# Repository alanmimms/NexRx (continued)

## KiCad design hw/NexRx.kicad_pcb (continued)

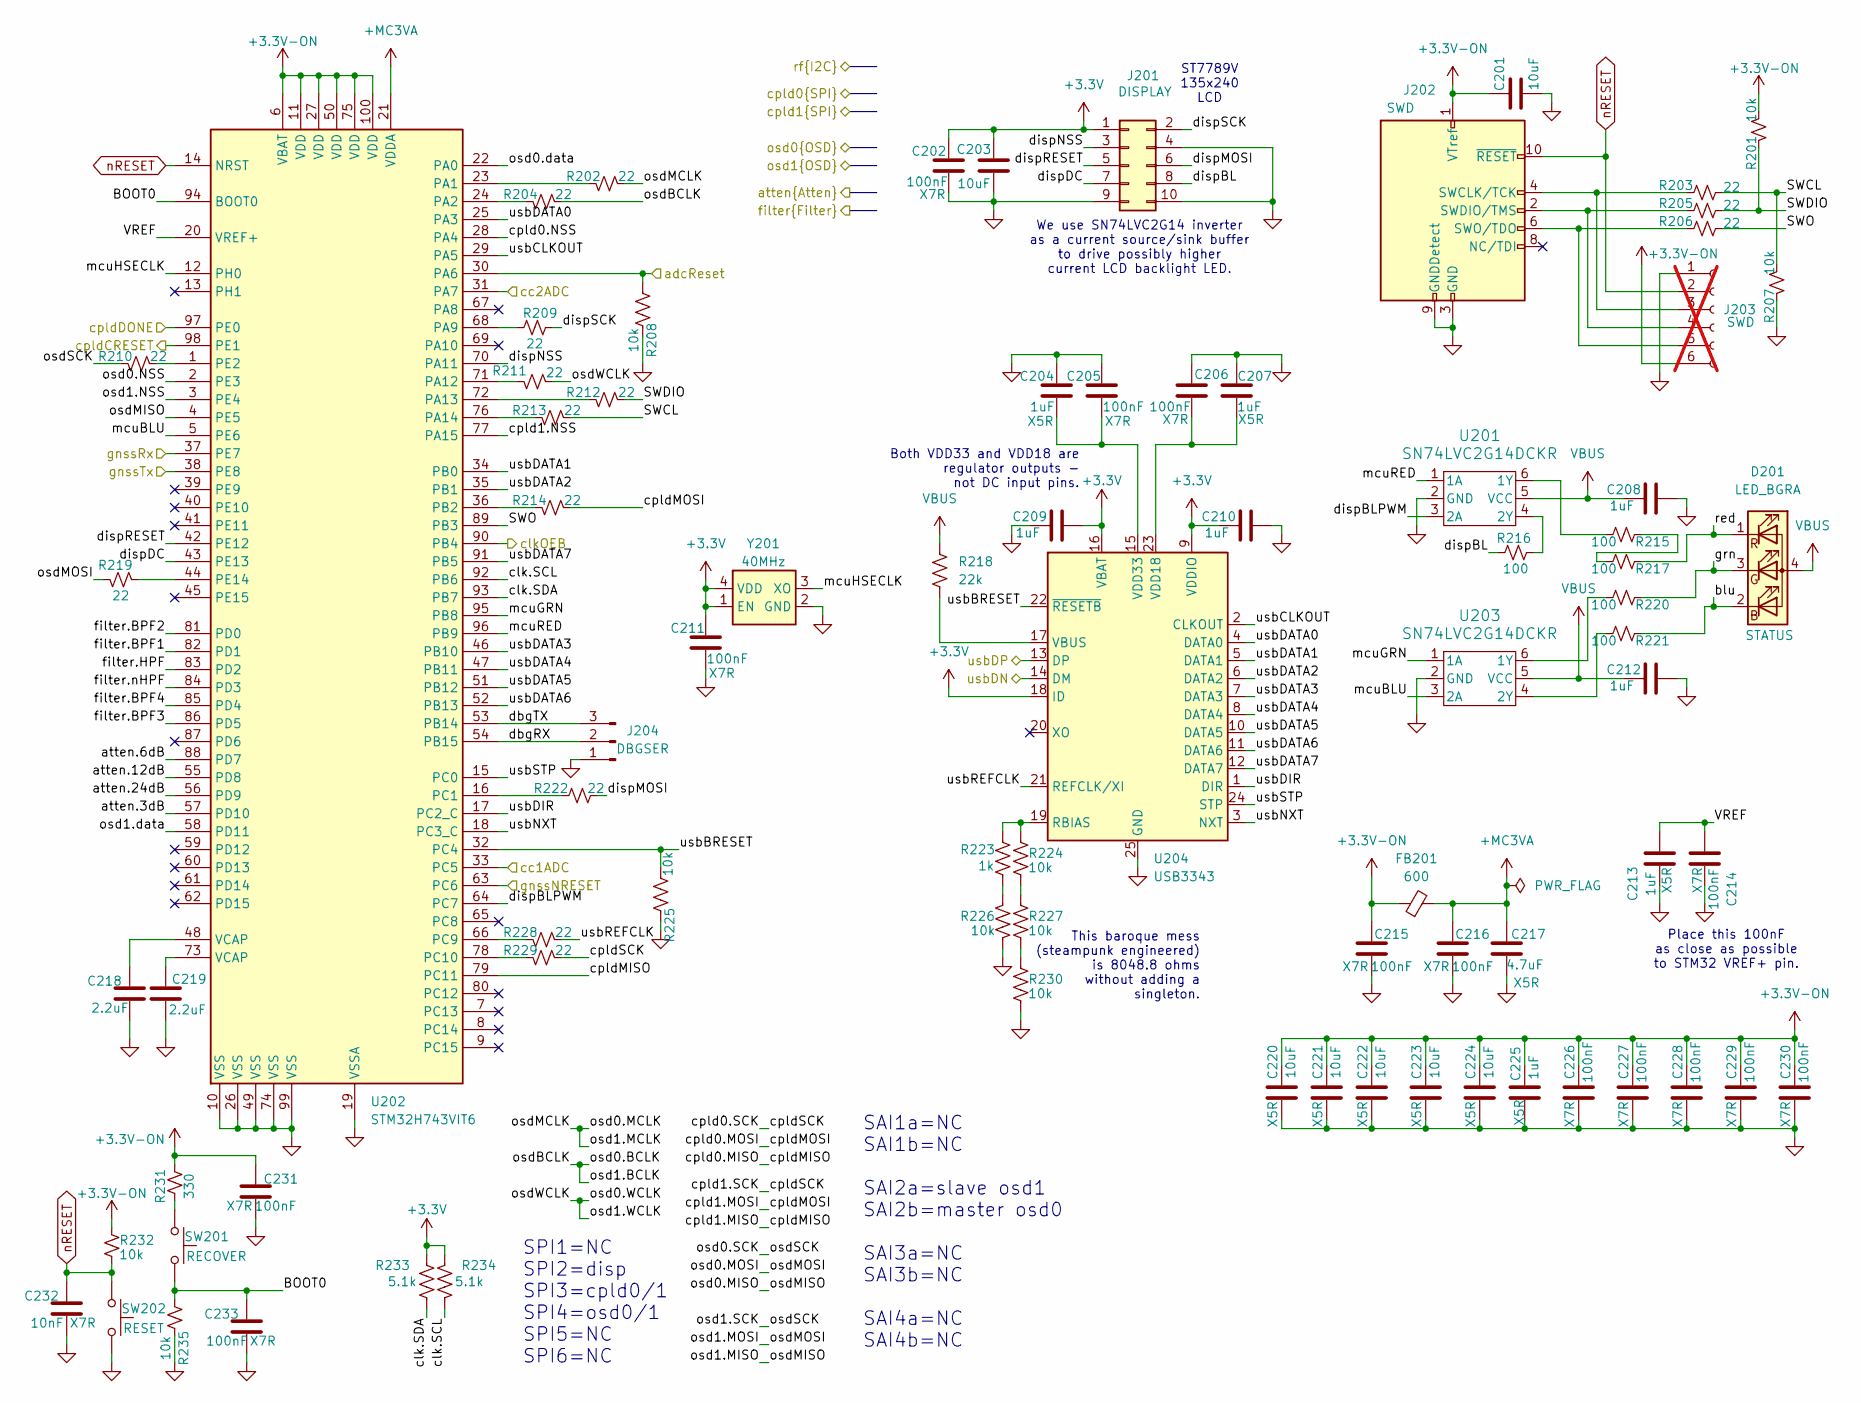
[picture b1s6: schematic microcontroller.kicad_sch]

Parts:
C201: 10uF; C_0402_1005Metric; MPN CL05A106MP6NUN8; LCSC_PN C76991
C202, C205, C206, C211, C215, C216, C230: 100nF; C_0402_1005Metric; MPN GCM155R71H104KE02D; LCSC_PN C307331
C203, C220, C221, C222, C223, C224: 10uF; C_0402_1005Metric; Mouser Part Number 187-CL05A106MP6NUN8
C204, C207, C208, C209, C210, C212: 1uF; C_0402_1005Metric; Mouser Part Number 81-GRM155R61E105MA2D
C213, C225: 1uF; C_0402_1005Metric; MPN GRM155R61E105MA12D; LCSC_PN C77009
C214, C226, C227, C228, C229, C231, C233: 100nF; C_0402_1005Metric; Mouser Part Number 81-GCM155R71H104KE2D
C217: 4.7uF; C_0402_1005Metric; MPN CM05X5R475M10AH; LCSC_PN C23733
C218, C219: 2.2uF; C_0402_1005Metric; MPN TMK105CBJ225MV-F; LCSC_PN C12530
C232: 10nF; C_0402_1005Metric; Mouser Part Number 81-GCM155R71H104KE2D
D201: LED_BGRA; WL-SFCD_0606; Mouser_PN 941-UHD1AA3K3E3V53Z3
FB201: 600; L_0603_1608Metric; MPN MI0603J601R-10; LCSC_PN C1006
J201: Conn_01x05_Pin; IDC-Header_2x05_P2.54mm_Vertical_SMD; LCSC_PN C32713285
J202: FTSH-105-01-L-DV-K; FTSH10501LDVK; MPN FTSH-105-01-L-DV-K; LCSC_PN C5155080
J203: SWD; PinHeader_1x06_P2.54mm_Vertical; not fitted
J204: DBGSER; PinHeader_1x03_P2.54mm_Vertical
R201, R207, R208, R224, R225, R226, R227, R230, R232, R235: 10k; R_0402_1005Metric; MPN RT0402BRD0710KL; LCSC_PN C283961
R202, R204: 22; R_0402_1005Metric; MPN 560112110216; LCSC_PN C25092
R203, R205, R206, R209, R210, R211, R212, R213, R214, R219, R222, R228, R229: 22; R_0402_1005Metric; MPN 560112110216; JLCPCBpn C4258780
R215, R216, R217, R220, R221: 100; R_0402_1005Metric; MPN MCS04020C1000FE000; Mouser Part Number 594-MCS04020C1000FE0
R218: 22k; R_0402_1005Metric; LCSC_PN C25768
R223: 1k; R_0402_1005Metric; MPN RP0402FRE071KL; LCSC_PN C11702
R231: 330; R_0402_1005Metric; MPN RC0402JR-7D330RL; LCSC_PN C25104
R233, R234: 5.1k; R_0402_1005Metric; MPN AC0402FR-7W5K1L; LCSC_PN C854378
SW201: RECOVER; SW_SPST_TS-1088-AR2016
SW202: RESET; SW_SPST_TS-1088-AR2016
U201, U203: SN74LVC2G14DCKR; SOIC_G14DCK3_TEX; LCSC_PN C37361
U202: STM32H743VIT6; LQFP-100_14x14mm_P0.5mm; MPN STM32H743VIT6; LCSC_PN C114409
U204: USB3343; QFN-24-1EP_4x4mm_P0.5mm_EP2.6x2.6mm; MPN USB3343-CP-TR; LCSC_PN C633347
Y201: 40MHz; ECSTXO201633400TR; MPN ECS-TXO-2016-33-400-TR; LCSC_PN C2451471

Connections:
+3.3V: C201.2, C202.1, C203.2, C209.2, C210.1, C211.1, C215.1, C220.1, C221.1, C222.1, C223.1, C224.1, C225.1, C226.1, C227.1, C228.1, C229.1, C230.1, C231.1, FB201.1, J201.1, J202.1 (VTref), J203.6, R201.1, R231.1, R232.1, R233.1, R234.1, U202.6 (VBAT), U202.11 (VDD), U202.27 (VDD), U202.50 (VDD), U202.75 (VDD), U202.100 (VDD), U204.9 (VDDIO), U204.16 (VBAT), U204.18 (ID), Y201.1 (EN), Y201.4 (VDD); also elsewhere on the board
+MC3VA: C216.1, C217.1, FB201.2, U202.21 (VDDA)
/Clock/clkOEB: U202.90 (PB4); also elsewhere on the board
/Filters/en.BPF1: U202.82 (PD1); also elsewhere on the board
/Filters/en.BPF2: U202.81 (PD0); also elsewhere on the board
/Filters/en.BPF3: U202.86 (PD5); also elsewhere on the board
/Filters/en.BPF4: U202.85 (PD4); also elsewhere on the board
/Filters/en.HPF: U202.83 (PD2); also elsewhere on the board
/Filters/en.nHPF: U202.84 (PD3); also elsewhere on the board
/Power/cc1ADC: U202.33 (PC5); also elsewhere on the board
/Power/cc2ADC: U202.31 (PA7); also elsewhere on the board
/Power/usbDN: U204.14 (DM); also elsewhere on the board
/Power/usbDP: U204.13 (DP); also elsewhere on the board
/atten.3dB: U202.57 (PD10); also elsewhere on the board
/atten.6dB: U202.88 (PD7); also elsewhere on the board
/atten.12dB: U202.55 (PD8); also elsewhere on the board
/atten.24dB: U202.56 (PD9); also elsewhere on the board
/cpld0/cpld.NSS: U202.28 (PA4); also elsewhere on the board
/cpld0/cpldCRESET: U202.98 (PE1); also elsewhere on the board
/cpld0/cpldDONE: U202.97 (PE0); also elsewhere on the board
/cpld0/osd.NSS: U202.2 (PE3); also elsewhere on the board
/cpld0/osd.data: U202.22 (PA0); also elsewhere on the board
/cpld1/cpld.MISO: U202.79 (PC11); also elsewhere on the board
/cpld1/cpld.MOSI: R214.1; also elsewhere on the board
/cpld1/cpld.NSS: U202.77 (PA15); also elsewhere on the board
/cpld1/cpld.SCK: R229.1; also elsewhere on the board
/cpld1/osd.BCLK: R204.1; also elsewhere on the board
/cpld1/osd.MCLK: R202.1; also elsewhere on the board
/cpld1/osd.MISO: U202.4 (PE5); also elsewhere on the board
/cpld1/osd.MOSI: R219.2; also elsewhere on the board
/cpld1/osd.NSS: U202.3 (PE4); also elsewhere on the board
/cpld1/osd.SCK: R210.2; also elsewhere on the board
/cpld1/osd.WCLK: R211.2; also elsewhere on the board
/cpld1/osd.data: U202.58 (PD11); also elsewhere on the board
/microcontroller/BOOT0: C233.1, R235.1, SW201.2, U202.94 (BOOT0)
/microcontroller/SWCL: R203.2, R207.1, R213.1
/microcontroller/SWDIO: R201.2, R205.2, R212.1
/microcontroller/SWO: R206.2, U202.89 (PB3)
/microcontroller/VREF: C213.1, C214.1, U202.20 (VREF+)
/microcontroller/adcReset: R208.1, U202.30 (PA6); also elsewhere on the board
/microcontroller/blu: D201.2 (BK), R221.1
/microcontroller/clk.SCL: R234.2, U202.92 (PB6)
/microcontroller/clk.SDA: R233.2, U202.93 (PB7)
/microcontroller/dbgRX: J204.2, U202.54 (PB15)
/microcontroller/dbgTX: J204.3, U202.53 (PB14)
/microcontroller/dispBL: J201.8, R216.2
/microcontroller/dispBLPWM: U201.3 (2A), U202.64 (PC7)
/microcontroller/dispDC: J201.7, U202.43 (PE13)
/microcontroller/dispMOSI: J201.6, R222.2
/microcontroller/dispNSS: J201.3, U202.70 (PA11)
/microcontroller/dispRESET: J201.5, U202.42 (PE12)
/microcontroller/dispSCK: J201.2, R209.2
/microcontroller/gnssNRESET: U202.63 (PC6); also elsewhere on the board
/microcontroller/gnssRx: U202.37 (PE7); also elsewhere on the board
/microcontroller/gnssTx: U202.38 (PE8); also elsewhere on the board
/microcontroller/grn: D201.3 (GK), R220.1
/microcontroller/mcuBLU: U202.5 (PE6), U203.3 (2A)
/microcontroller/mcuGRN: U202.95 (PB8), U203.1 (1A)
/microcontroller/mcuHSECLK: U202.12 (PH0), Y201.3 (XO)
/microcontroller/mcuRED: U201.1 (1A), U202.96 (PB9)
/microcontroller/red: D201.1 (RK), R217.1
/microcontroller/usbBRESET: R225.1, U202.32 (PC4), U204.22 (~RESETB)
/microcontroller/usbCLKOUT: U202.29 (PA5), U204.2 (CLKOUT)
/microcontroller/usbDATA0: U202.25 (PA3), U204.4 (DATA0)
/microcontroller/usbDATA1: U202.34 (PB0), U204.5 (DATA1)
/microcontroller/usbDATA2: U202.35 (PB1), U204.6 (DATA2)
/microcontroller/usbDATA3: U202.46 (PB10), U204.7 (DATA3)
/microcontroller/usbDATA4: U202.47 (PB11), U204.8 (DATA4)
/microcontroller/usbDATA5: U202.51 (PB12), U204.10 (DATA5)
/microcontroller/usbDATA6: U202.52 (PB13), U204.11 (DATA6)
/microcontroller/usbDATA7: U202.91 (PB5), U204.12 (DATA7)
/microcontroller/usbDIR: U202.17 (PC2_C), U204.1 (DIR)
/microcontroller/usbNXT: U202.18 (PC3_C), U204.3 (NXT)
/microcontroller/usbREFCLK: R228.1, U204.21 (REFCLK/XI)
/microcontroller/usbSTP: U202.15 (PC0), U204.24 (STP)
GND: C201.1, C202.2, C203.1, C204.2, C205.1, C206.1, C207.2, C208.2, C209.1, C210.2, C211.2, C212.2, C213.2, C214.2, C215.2, C216.2, C217.2, C218.2, C219.2, C220.2, C221.2, C222.2, C223.2, C224.2, C225.2, C226.2, C227.2, C228.2, C229.2, C230.2, C231.2, C232.2, C233.2, J201.4, J201.9, J201.10, J202.3 (GND), J202.5 (GND), J202.9 (GNDDetect), J203.1, J204.1, R207.2, R208.2, R225.2, R226.2, R230.2, R235.2, SW202.2, U201.2 (GND), U202.10 (VSS), U202.19 (VSSA), U202.26 (VSS), U202.49 (VSS), U202.74 (VSS), U202.99 (VSS), U203.2 (GND), U204.25 (GND), Y201.2 (GND); also elsewhere on the board
unnamed: C218.1, U202.48 (VCAP)
unnamed: C219.1, U202.73 (VCAP)
unnamed: J202.4 (SWCLK/TCK), J203.3, R203.1
unnamed: J202.2 (SWDIO/TMS), J203.4, R205.1
unnamed: J202.6 (SWO/TDO), J203.5, R206.1
unnamed: R215.1, R217.2
unnamed: R223.2, R226.1
unnamed: R224.2, R227.1
unnamed: R227.2, R230.1
unnamed: R231.2, SW201.1
unnamed: R215.2, U201.6 (1Y)
unnamed: R216.1, U201.4 (2Y)
unnamed: R202.2, U202.23 (PA1)
unnamed: R204.2, U202.24 (PA2)
unnamed: R209.1, U202.68 (PA9)
unnamed: R211.1, U202.71 (PA12)
unnamed: R212.2, U202.72 (PA13)
unnamed: R213.2, U202.76 (PA14)
unnamed: R214.2, U202.36 (PB2)
unnamed: R222.1, U202.16 (PC1)
unnamed: R228.2, U202.66 (PC9)
unnamed: R229.2, U202.78 (PC10)
unnamed: R210.1, U202.1 (PE2)
unnamed: R219.1, U202.44 (PE14)
unnamed: R220.2, U203.6 (1Y)
unnamed: R221.2, U203.4 (2Y)
unnamed: R223.1, R224.1, U204.19 (RBIAS)
unnamed: R218.2, U204.17 (VBUS)
unnamed: C206.2, C207.1, U204.23 (VDD18)
unnamed: C204.1, C205.2, U204.15 (VDD33)
VBUS: C208.1, C212.1, D201.4 (A), R218.1, U201.5 (VCC), U203.5 (VCC); also elsewhere on the board
nRESET: C232.1, J202.10 (~RESET), J203.2, R232.2, SW202.1, U202.14 (NRST)

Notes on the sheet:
SPI1=NC SPI2=disp SPI3=cpld0/1 SPI4=osd0/1 SPI5=NC SPI6=NC
This baroque mess (steampunk engineered) is 8048.8 ohms without adding a singleton.
Both VDD33 and VDD18 are regulator outputs - not DC input pins.
SAI1a=NC SAI1b=NC SAI2a=slave osd1 SAI2b=master osd0 SAI3a=NC SAI3b=NC SAI4a=NC SAI4b=NC
We use SN74LVC2G14 inverter as a current source/sink buffer to drive possibly higher current LCD backlight LED.
Place this 100nF as close as possible to STM32 VREF+ pin.
ST7789V 135x240 LCD

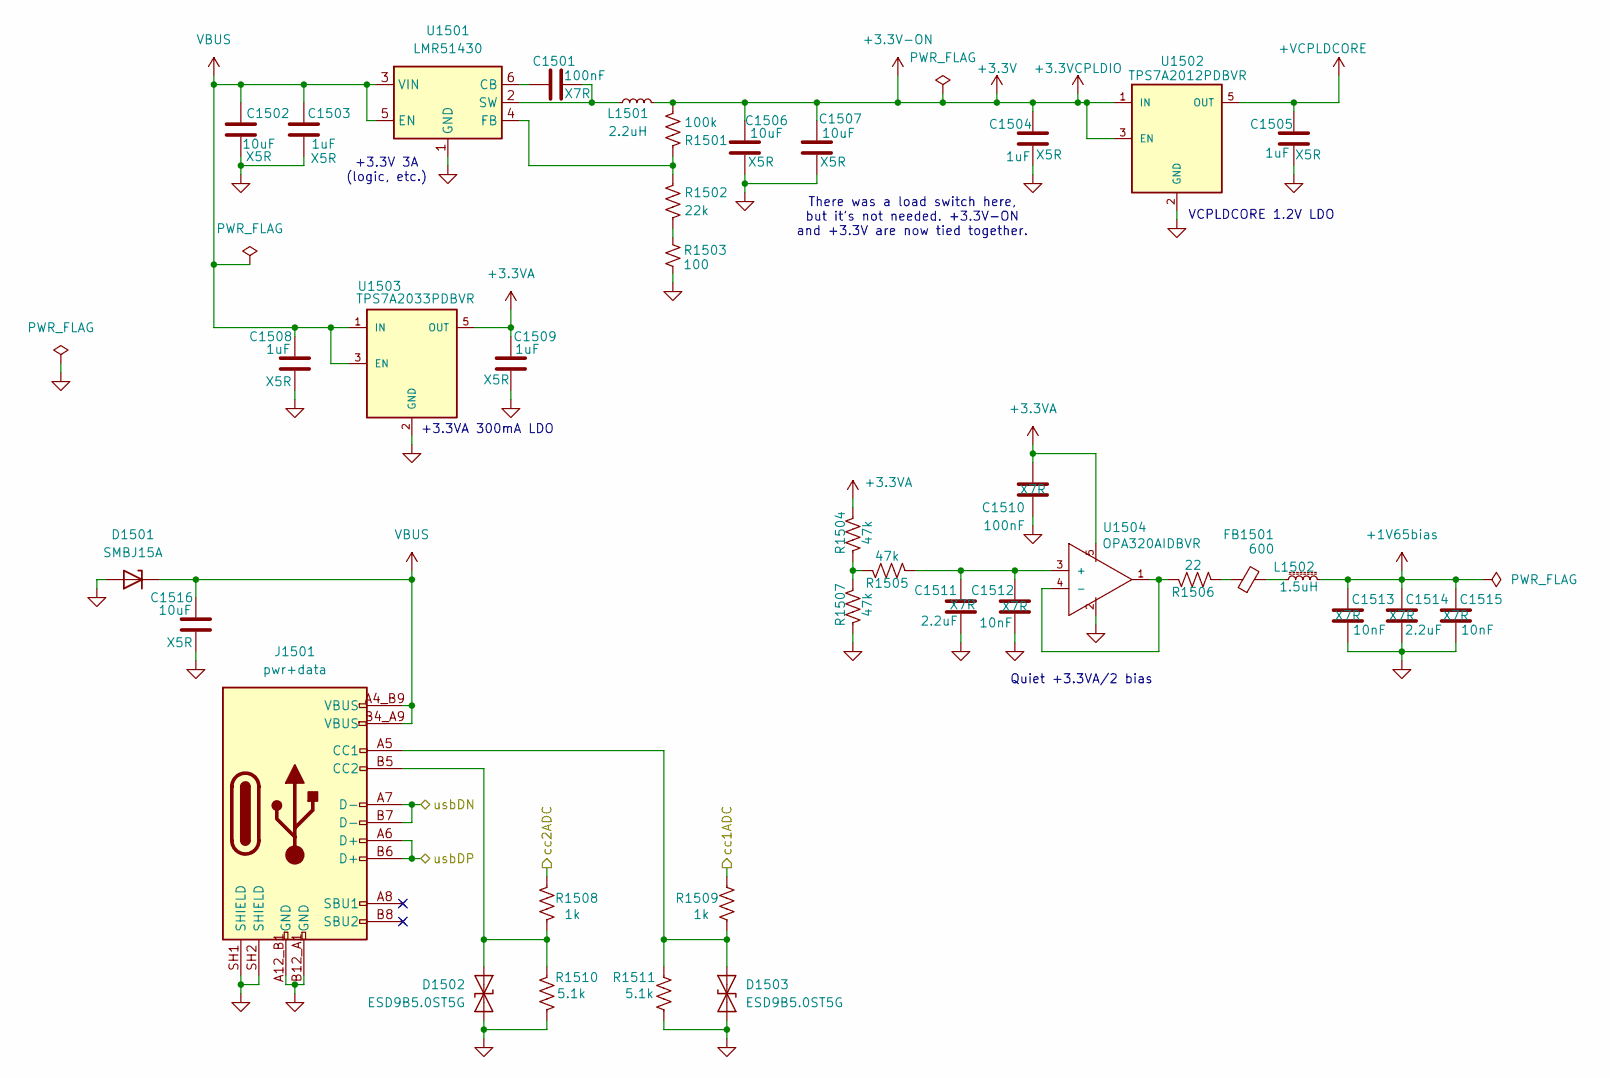
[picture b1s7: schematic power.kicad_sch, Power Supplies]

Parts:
C1501, C1510: 100nF; C_0402_1005Metric; MPN GCM155R71H104KE02D; LCSC_PN C307331
C1502, C1516: 10uF; C_0603_1608Metric; MPN CL10A106MA8NRWC; LCSC_PN C76614
C1503, C1505: 1uF; C_0402_1005Metric; MPN GRM155R61E105MA12D; LCSC_PN C77009
C1504, C1508, C1509: 1uF; C_0402_1005Metric; Mouser Part Number 81-GRM155R61E105MA2D
C1506, C1507: 10uF; C_0603_1608Metric; Mouser Part Number 187-CL10A106MA8NRWC
C1511, C1514: 2.2uF; C_0402_1005Metric; MPN TMK105CBJ225MV-F; LCSC_PN C12530
C1512, C1513, C1515: 10nF; C_0402_1005Metric; MPN CC0402KRX5R8BB103; LCSC_PN C15195
D1501: SMBJ15A; D_SMB; MPN 1.0SMBJ15A-AQ; LCSC_PN C83846
D1502, D1503: ESD9B5.0ST5G; D_SOD-923; MPN ESD9B5.0ST5G; LCSC_PN C111566
FB1501: 600; L_0603_1608Metric; MPN MI0603J601R-10; LCSC_PN C1006
J1501: pwr+data; SAMESKY_UJ20-C-H-G-SMT-1-P16-TR; MPN UJ20-C-H-G-SMT-1-P16-TR; LCSC_PN C45082766
L1501: 2.2uH; L_0805_2012Metric; MPN 74479275222; LCSC_PN C341781
L1502: 1.5uH; L_0603_1608Metric; LCSC_PN C73201
R1501: 100k; R_0402_1005Metric; MPN RP0402BRD07100KL; LCSC_PN C25741
R1502: 22k; R_0402_1005Metric; LCSC_PN C25768
R1503: 100; R_0402_1005Metric; MPN MCS04020C1000FE000; Mouser Part Number 594-MCS04020C1000FE0
R1504, R1505, R1507: 47k; R_0402_1005Metric; MPN RC0402FR-7D47KL; JLCPCBpn C854337
R1506: 22; R_0402_1005Metric; MPN 560112110216; LCSC_PN C25092
R1508, R1509: 1k; R_0402_1005Metric; MPN RP0402FRE071KL; LCSC_PN C11702
R1510, R1511: 5.1k; R_0402_1005Metric; MPN AC0402FR-7W5K1L; LCSC_PN C854378
U1501: LMR51430; SOT-23-6; MPN MR51430YDDCR; LCSC_PN C5210749
U1502: TPS7A2012PDBVR; DBV0005A-MFG; MPN TPS7A2012PDBVR; LCSC_PN C2864597
U1503: TPS7A2033PDBVR; DBV0005A-MFG; MPN TPS7A2033PDBVR; LCSC_PN C2862740
U1504: OPA320AIDBVR; SOT95P280X145-5N; MPN OPA320AIDBVR; Mouser Part Number 595-OPA320AIDBVR

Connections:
+1V65bias: C1513.1, C1514.1, C1515.1, L1502.2; also elsewhere on the board
+3.3V: C1504.1, C1506.1, C1507.1, L1501.2, R1501.2, U1502.1 (IN), U1502.3 (EN); also elsewhere on the board
+3.3VA: C1509.1, C1510.1, R1504.2, U1503.5 (OUT), U1504.5; also elsewhere on the board
+VCPLDCORE: C1505.1, U1502.5 (OUT); also elsewhere on the board
/Power/cc1ADC: R1509.1; also elsewhere on the board
/Power/cc2ADC: R1508.1; also elsewhere on the board
/Power/usbDN: J1501.A7 (D-), J1501.B7 (D-); also elsewhere on the board
/Power/usbDP: J1501.A6 (D+), J1501.B6 (D+); also elsewhere on the board
GND: C1502.2, C1503.2, C1504.2, C1505.2, C1506.2, C1507.2, C1508.2, C1509.2, C1510.2, C1511.2, C1512.2, C1513.2, C1514.2, C1515.2, C1516.2, D1501.2 (A), D1502.1 (A1), D1503.1 (A1), J1501.A12_B1 (GND), J1501.B12_A1 (GND), J1501.SH1 (SHIELD), J1501.SH2 (SHIELD), R1503.2, R1507.1, R1510.2, R1511.2, U1501.1 (GND), U1502.2 (GND), U1503.2 (GND), U1504.2; also elsewhere on the board
unnamed: D1502.2 (A2), J1501.B5 (CC2), R1508.2, R1510.1
unnamed: D1503.2 (A2), J1501.A5 (CC1), R1509.2, R1511.1
unnamed: FB1501.1, R1506.1
unnamed: FB1501.2, L1502.1
unnamed: R1502.1, R1503.1
unnamed: R1504.1, R1505.2, R1507.2
unnamed: C1501.1, U1501.6 (CB)
unnamed: R1501.1, R1502.2, U1501.4 (FB)
unnamed: C1501.2, L1501.1, U1501.2 (SW)
unnamed: C1511.1, C1512.1, R1505.1, U1504.3 (+)
unnamed: R1506.2, U1504.1, U1504.4 (-)
VBUS: C1502.1, C1503.1, C1508.1, C1516.1, D1501.1 (K), J1501.A4_B9 (VBUS), J1501.B4_A9 (VBUS), U1501.3 (VIN), U1501.5 (EN), U1503.1 (IN), U1503.3 (EN); also elsewhere on the board

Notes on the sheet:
VCPLDCORE 1.2V LDO
Quiet +3.3VA/2 bias
There was a load switch here, but it's not needed. +3.3V-ON and +3.3V are now tied together.
+3.3V 3A (logic, etc.)
+3.3VA 300mA LDO

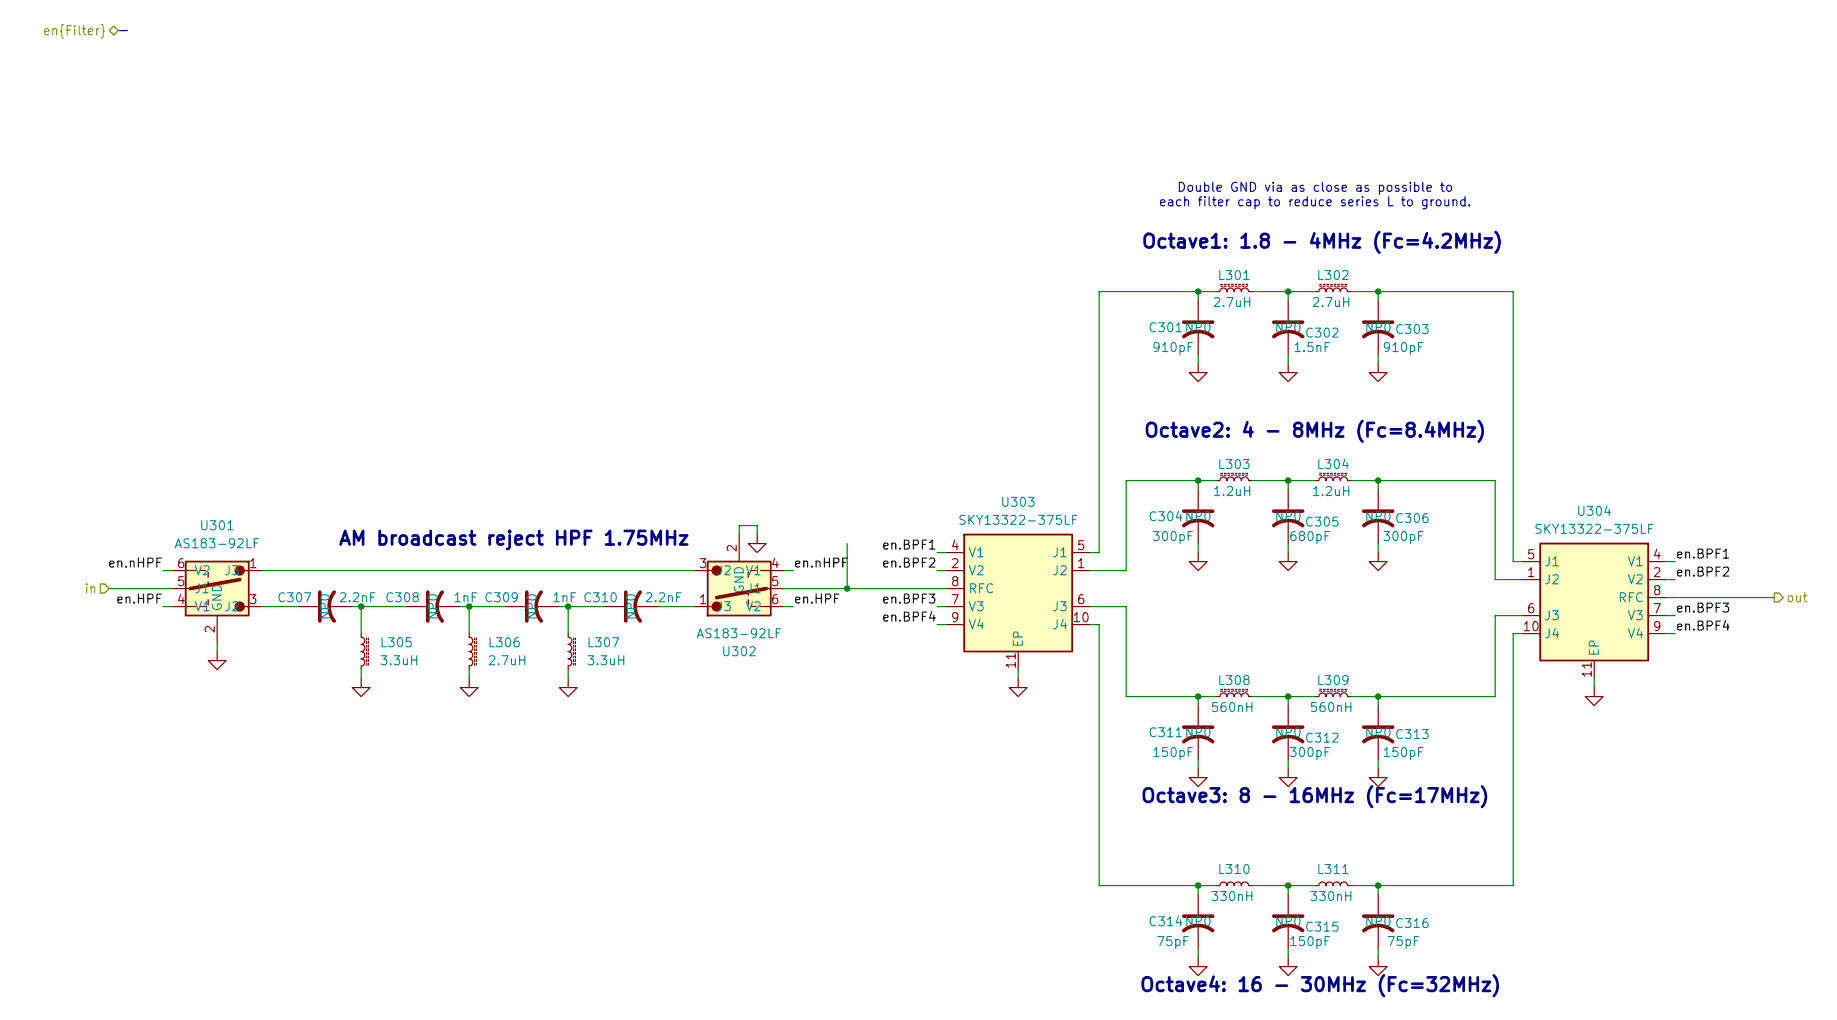
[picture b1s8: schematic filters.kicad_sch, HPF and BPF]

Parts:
C301, C303: 910pF; C_0603_1608Metric; Mouser Part Number 791-0603N911J250CT
C302: 1.5nF; C_0402_1005Metric; Mouser Part Number 80-C0402C152J3GACAUTO
C304, C306, C312: 300pF; C_0402_1005Metric; Mouser Part Number 80-C0402C301J3GACTU
C305: 680pF; C_0402_1005Metric; Mouser Part Number 81-GRT1555C1E681JA02J
C307, C310: 2.2nF; C_0402_1005Metric; Mouser Part Number 80-C0402C222K3GECTU
C308, C309: 1nF; C_0402_1005Metric; Mouser Part Number 81-GRT1555C1E102JA02J
C311, C313, C315: 150pF; C_0402_1005Metric; Mouser Part Number C0402C151J3GACTU
C314, C316: 75pF; C_0402_1005Metric; Mouser Part Number 80-CBR04C750G3GAC
L301, L302, L306: 2.7uH; L_1812_4532Metric; Mouser Part Number 994-1812CS-272XJRC
L303, L304: 1.2uH; L_1812_4532Metric; Mouser Part Number 994-1812CS-122XJRC
L305, L307: 3.3uH; L_1812_4532Metric; Mouser Part Number 994-1812CS-332XJRC
L308, L309: 560nH; L_1008_2520Metric_Pad1.43x2.20mm_HandSolder-keepout; Mouser Part Number 994-1008CS-561XJRC
L310, L311: 330nH; L_Coilcraft_2929SQ-331; MPN 2929SQ-331JEC; LCSC_PN C20623511
U301, U302: AS183-92LF; SOT65P220X110-6N; MPN AS183-92LF; LCSC_PN C2654768
U303, U304: SKY13322-375LF; SON50P200X300X50-11N-D; Mouser Part Number 873-SKY13322-375LF

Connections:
/Filters/en.BPF1: U303.4 (V1), U304.4 (V1); also elsewhere on the board
/Filters/en.BPF2: U303.2 (V2), U304.2 (V2); also elsewhere on the board
/Filters/en.BPF3: U303.7 (V3), U304.7 (V3); also elsewhere on the board
/Filters/en.BPF4: U303.9 (V4), U304.9 (V4); also elsewhere on the board
/Filters/en.HPF: U301.4 (V1), U302.6 (V2); also elsewhere on the board
/Filters/en.nHPF: U301.6 (V2), U302.4 (V1); also elsewhere on the board
/Filters/in: U301.5 (J1); also elsewhere on the board
/Filters/out: U304.8 (RFC); also elsewhere on the board
GND: C301.2, C302.2, C303.2, C304.2, C305.2, C306.2, C311.2, C312.2, C313.2, C314.2, C315.2, C316.2, L305.2, L306.2, L307.2, U301.2 (GND), U302.2 (GND), U303.11 (EP), U304.11 (EP); also elsewhere on the board
unnamed: C302.1, L301.2, L302.1
unnamed: C305.1, L303.2, L304.1
unnamed: C307.2, C308.1, L305.1
unnamed: C308.2, C309.1, L306.1
unnamed: C309.2, C310.1, L307.1
unnamed: C312.1, L308.2, L309.1
unnamed: C315.1, L310.2, L311.1
unnamed: C307.1, U301.3 (J2)
unnamed: U301.1 (J3), U302.3 (J2)
unnamed: U302.5 (J1), U303.8 (RFC)
unnamed: C310.2, U302.1 (J3)
unnamed: C301.1, L301.1, U303.5 (J1)
unnamed: C304.1, L303.1, U303.1 (J2)
unnamed: C311.1, L308.1, U303.6 (J3)
unnamed: C314.1, L310.1, U303.10 (J4)
unnamed: C303.1, L302.2, U304.5 (J1)
unnamed: C306.1, L304.2, U304.1 (J2)
unnamed: C313.1, L309.2, U304.6 (J3)
unnamed: C316.1, L311.2, U304.10 (J4)

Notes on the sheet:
Double GND via as close as possible to each filter cap to reduce series L to ground.
Octave3: 8 - 16MHz (Fc=17MHz)
Octave1: 1.8 - 4MHz (Fc=4.2MHz)
AM broadcast reject HPF 1.75MHz
Octave2: 4 - 8MHz (Fc=8.4MHz)
Octave4: 16 - 30MHz (Fc=32MHz)

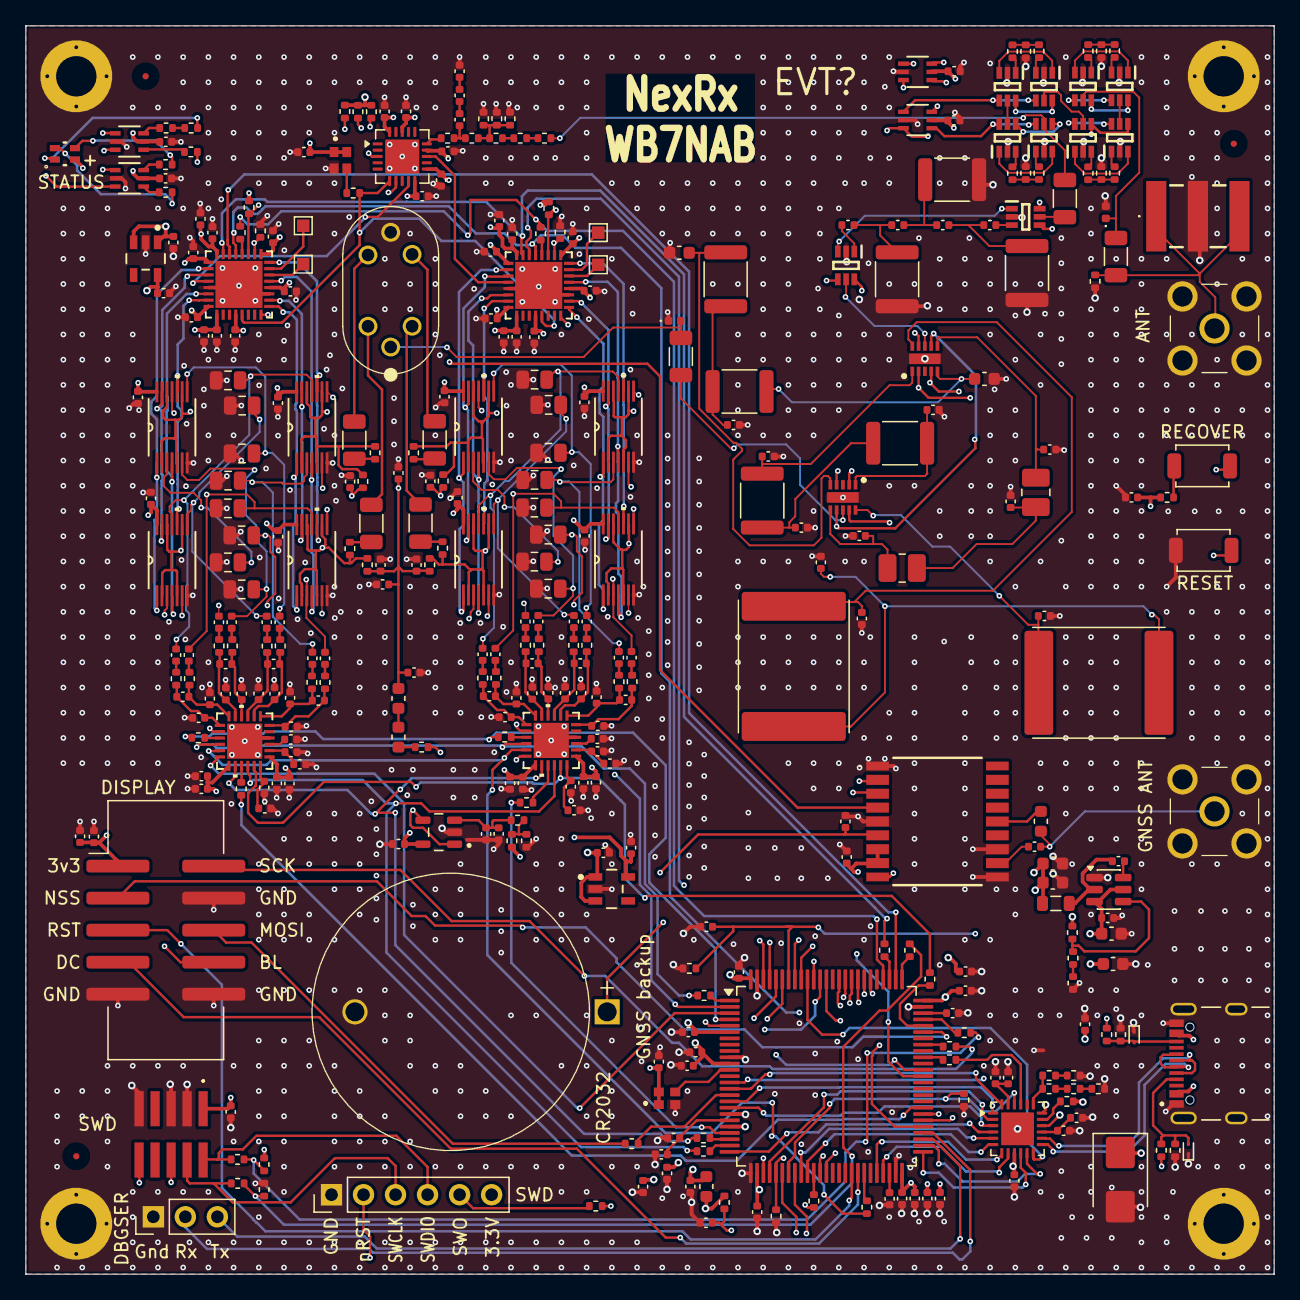
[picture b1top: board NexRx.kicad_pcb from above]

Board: 6 copper layers, 99.0 x 99.0 mm, 376 parts (0 on the bottom side), 279 nets.

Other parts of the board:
R501, R502: 16.5; R_0402_1005Metric
R503: 66.5; R_0402_1005Metric
R601, R602: 30.1; R_0402_1005Metric
R603: 26.7; R_0402_1005Metric
R701, R702: 44.2; R_0402_1005Metric
R703: 6.34; R_0402_1005Metric

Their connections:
GND: R503.2, R603.2, R703.2; also elsewhere on the board
unnamed: R501.1, R502.2, R503.1
unnamed: R601.1, R602.2, R603.1
unnamed: R701.1, R702.2, R703.1
unnamed 214: R501.2; also elsewhere on the board
unnamed 216: R502.1; also elsewhere on the board
unnamed 217: R601.2; also elsewhere on the board
unnamed 219: R602.1; also elsewhere on the board
unnamed 220: R701.2; also elsewhere on the board
unnamed 222: R702.1; also elsewhere on the board

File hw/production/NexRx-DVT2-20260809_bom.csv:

Designator,Footprint,Quantity,Value,LCSC Part #
BT101,S8401-46,1,CR3032 holder,C5904513
"C1001, C1002, C1401, C1402, C212, C806, C810, C819, C824, C831, C834, C838, C840, C906, C910, C919, C924, C931, C934, C938, C940",0402,21,4.7uF,
"C1003, C1004, C1005, C1006, C1007, C1008, C1009, C107, C108, C1201, C1202, C1203, C1204, C1205, C1206, C1403, C1404, C1405, C1406, C1407, C1408, C1409, C1501, C1511, C207, C208, C210, C211, C216, C227, C228, C229, C230, C231, C232, C233, C317, C802, C803, C804, C809, C811, C818, C822, C837, C843, C844, C902, C903, C904, C909, C911, C918, C922, C937, C943, C944",0402,57,100nF,
"C101, C102, C103, C825, C845, C925, C945",1206,7,100nF,GRM3195C2A104JA01D
"C104, C105",0402,2,10uF,C479655
"C106, C311, C313, C813, C814, C827, C828, C835, C836, C841, C842, C913, C914, C927, C928, C935, C936, C941, C942",0402,19,150pF,
"C1207, C1208, C1209, C204, C205, C217, C218",0402,7,27pF,
"C1502, C1506, C1507, C1517",0603,4,10uF,
"C1503, C1504, C1505, C1509, C1510, C206, C209, C213, C214, C215, C226, C801, C816, C901, C916",0402,15,1uF,
C1508,0402,1,200pF,
"C1512, C1515, C219, C220",0402,4,2.2uF,
"C1513, C1514, C1516",0402,3,10nF,
"C201, C202, C203, C221, C222, C223, C224, C225, C805, C808, C812, C905, C908, C912",0402,14,10uF,
"C301, C303",0402,2,910pF,
C302,0402,1,1.5nF,
"C304, C306, C312",0402,3,300pF,
C305,0402,1,620pF,
"C307, C310, C807, C821, C833, C839, C907, C921, C933, C939",0402,10,2.2nF,
"C308, C309",0402,2,1nF,
"C314, C316",0402,2,75pF,
C315,0402,1,160pF,
"C815, C817, C820, C823, C826, C829, C830, C832, C915, C917, C920, C923, C926, C929, C930, C932",0805,16,8nF 1%,
D101,D_SOD-882,1,TPD1E0B04DPY,
D102,0402,1,SP0402B-ELC-01ETG,SP0402B-ELC-01ETG
D1501,D_SMB,1,SMBJ15A,SMBJ15A
"D1502, D1503",D_SOD-923,2,ESD9B5.0ST5G,
D201,UHD111AFKAC3K23E1L3VG5ZB3Z3,1,LED_BGRA,UHD111A-FKA-C3K23E1L3VG5ZB3Z3
"FB1501, FB201",0603,2,600,MI0603J601R-10
GD101,GDT3535S1RP,1,350V,GDT35-35-S1-RP
"J101, J102",733910083,2,SMA,733910083
J1501,USB_C_Receptacle_HRO_TYPE-C-31-M-12-bursted,1,pwr+data,TYPE-C-31-M-12
J201,68710814022,1,68710814022,5034800800
J202,FTSH10501LDVK,1,FTSH-105-01-L-DV-K,
L101,0603,1,47nH,C98076
L1501,0805,1,2.2uH,
L1502,1210,1,1.5uH,NLV32T-1R5J-EF
"L301, L302",1812,2,2.7uH,1812CS-332XJR
"L303, L304",1812,2,1.2uH,1812CS-122XJR
"L305, L307",1812,2,3.3uH,1812CS-332XJR
L306,1812,1,2.7uH,1812CS-272XJR
"L308, L309",1008,2,560nH,1008CS-561XJR
"L310, L311",1008,2,330nH,1008CS-331XJR
"R1001, R1401, R1502, R218",0402,4,22.1k,
"R1002, R1402, R201, R204, R205, R225, R803, R813, R903, R913",0402,10,10k,
"R1003, R1201, R1403, R202, R203, R206, R207, R208, R212, R213, R216, R217, R219, R220, R806, R808, R906, R908",0402,18,22,
R101,0402,1,100k,ERJ-P08J104V
"R1202, R1207, R1208, R1209, R222",0402,5,330,
"R1203, R1204, R1205, R1206, R1501",0402,5,100k,
"R1503, R1504, R1506",0402,3,47k,
R1505,0402,1,34.4,
"R1507, R1508",0402,2,1k,
"R1509, R1510, R223, R224",0402,4,5.1k,
"R209, R210, R211, R214, R215, R801, R802, R804, R805, R809, R810, R811, R812, R901, R902, R904, R905, R909, R910, R911, R912",0402,21,100,
R221,0402,1,8.06k,
"R401, R402",0402,2,8.66,
R403,0402,1,143,
"R501, R502",0402,2,16.5,
R503,0402,1,66.5,
"R601, R602",0402,2,30.1,
R603,0402,1,26.7,
"R701, R702",0402,2,44.2,
R703,0402,1,6.34,
"R807, R814, R907, R914",0402,4,10,
SW201,Panasonic_EVQPUK_EVQPUB,1,Push button switch,
T101,Transformer-2P-2S-BN-43-202,1,"BN-43-202, 50:2x22 ohm, 3 turns primary, 2 turns secondary trifilar #30 AWG",
"U1001, U1401",QFNS32_LAT,2,ICE40LP384-SG32,
"U101, U103, U309",SOIC_G14DCK3_TEX,3,SN74LVC2G14DCK3,
U102,ublox_MAX,1,GNSS module,C5117921
U1501,SON65P300X300X100-9N-D,1,TPS74612PQWDRBRQ1,TPS74612PQWDRBRQ1
U1502,SOT-23-6,1,LMR51430,
U1503,SOT95P280X145-6N,1,TPS22918DBVR,TPS22918DBVR
U1504,DBV0005A-MFG,1,TPS7A2033PDBVR,
U1505,SOT95P280X145-5N,1,OPA320AIDBVR,
U201,LQFP-100_14x14mm_P0.5mm,1,STM32H743VIT6,STM32H743VIT6
U202,QFN-24-1EP_4x4mm_P0.5mm_EP2.6x2.6mm,1,USB3343,USB3343-CP-TR
"U301, U302, U303, U304, U305, U306, U307, U308, U401, U402, U501, U502, U601, U602, U701, U702",SOT65P220X110-6N,16,AS183-92LF,AS183-92LF
"U801, U803, U804, U805, U901, U903, U904, U905",DGV14,8,SN74CBTLV3125RGYR,
"U802, U902",RTW24_4P15X4P15_TEX,2,TLV320ADC5140IRTWR,TLV320ADC5140IRTWR
Y1201,ECSTXO201633400TR,1,40MHz,ECS-TXO-2016-33-400-TR
Y1202,QFN-20-1EP_4x4mm_P0.5mm_EP2.7x2.7mm,1,Si5351C-B-GM,
"Y201, Y202",Crystal_SMD_2520-4Pin_2.5x2.0mm,2,26MHz,E2X260181G01

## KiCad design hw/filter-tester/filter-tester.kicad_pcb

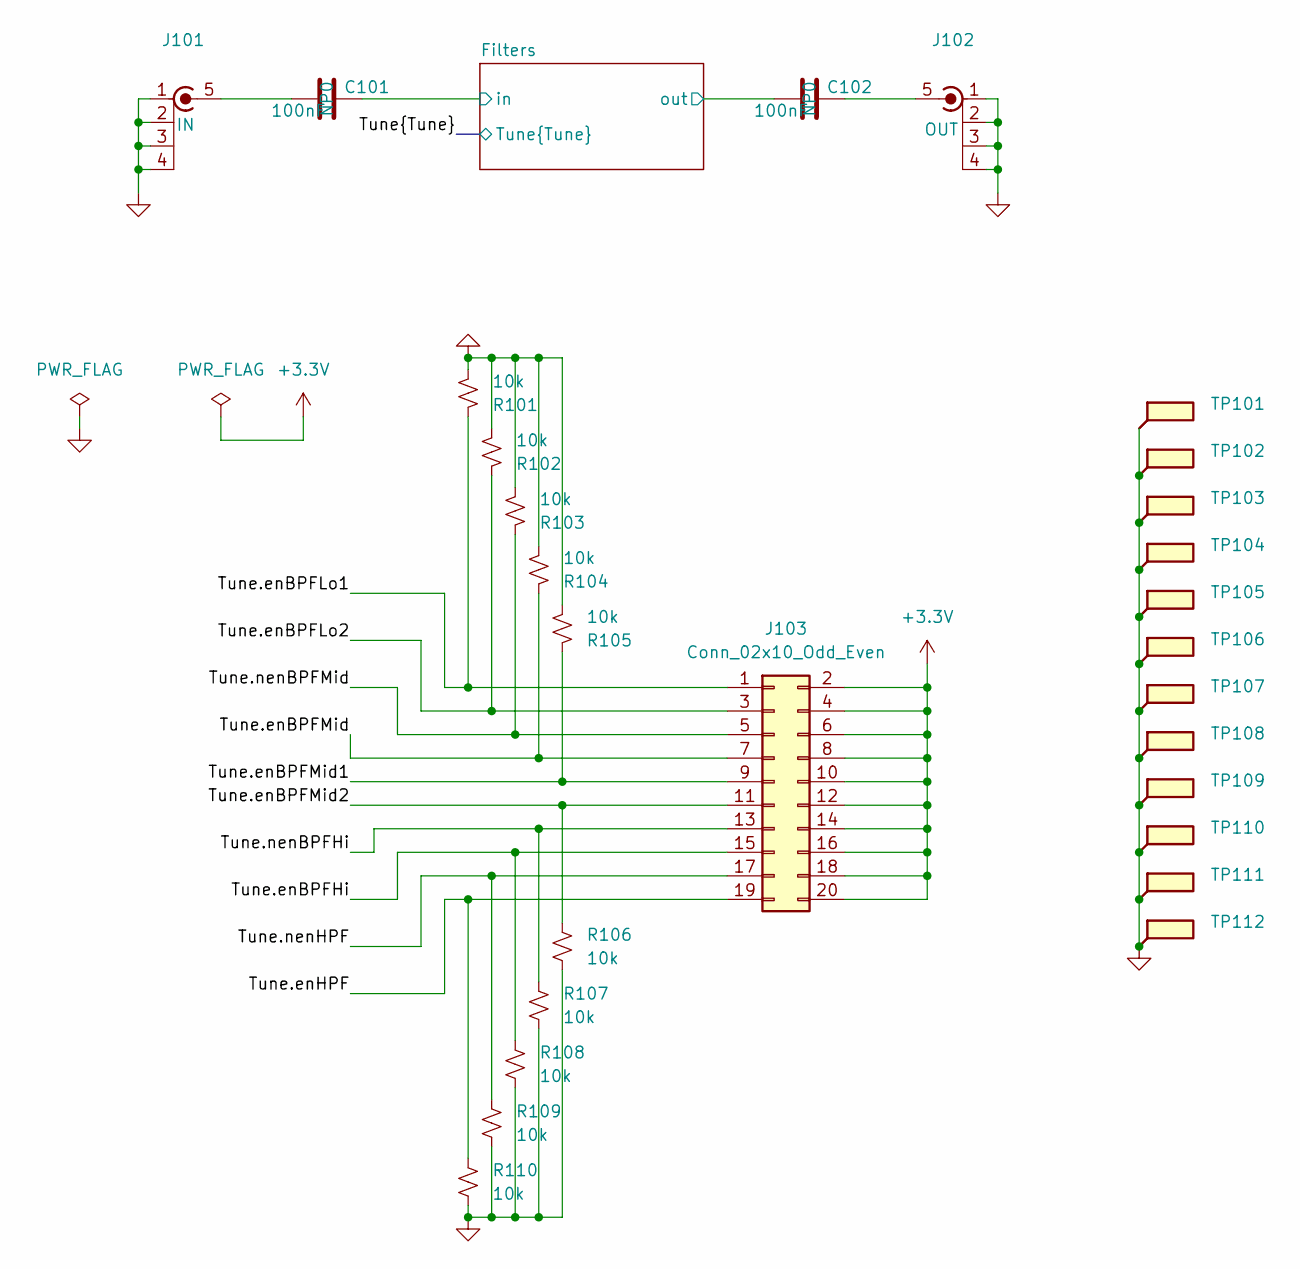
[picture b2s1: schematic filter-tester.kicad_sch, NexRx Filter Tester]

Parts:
C101, C102: 100nF; C_1206_3216Metric; MPN GRM3195C2A104JA01D; LCSC_PN C170182
J101, J102: SMA; 733910083; MPN 73391-0083; Mouser_PN 538-73391-0083
J103: Conn_02x10_Odd_Even; PinHeader_2x10_P2.54mm_Vertical_SMD; Mouser_PN 855-M20-8761046
R101, R102, R103, R104, R105, R106, R107, R108, R109, R110: 10k; R_0603_1608Metric; MPN RC0402JR-7D10KL; Mouser_PN 603-RC0402JR-7D10KL
TP101, TP102, TP103, TP104, TP105, TP106, TP107, TP108, TP109, TP110, TP111, TP112: GND; TestPoint_Pad_1.0x1.0mm

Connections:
+3.3V: J103.2, J103.4, J103.6, J103.8, J103.10, J103.12, J103.14, J103.16, J103.18, J103.20
/Filters/in: C101.1; also elsewhere on the board
/Filters/out: C102.2; also elsewhere on the board
/Tune.enBPFHi: J103.15, R108.1; also elsewhere on the board
/Tune.enBPFLo1: J103.1, R101.1; also elsewhere on the board
/Tune.enBPFLo2: J103.3, R102.1; also elsewhere on the board
/Tune.enBPFMid: J103.7, R104.1; also elsewhere on the board
/Tune.enBPFMid1: J103.9, R105.1; also elsewhere on the board
/Tune.enBPFMid2: J103.11, R106.1; also elsewhere on the board
/Tune.enHPF: J103.19, R110.1; also elsewhere on the board
/Tune.nenBPFHi: J103.13, R107.1; also elsewhere on the board
/Tune.nenBPFMid: J103.5, R103.1; also elsewhere on the board
/Tune.nenHPF: J103.17, R109.1; also elsewhere on the board
GND: J101.1 (In), J101.2 (Ext), J101.3 (Ext), J101.4 (Ext), J102.1 (In), J102.2 (Ext), J102.3 (Ext), J102.4 (Ext), R101.2, R102.2, R103.2, R104.2, R105.2, R106.2, R107.2, R108.2, R109.2, R110.2, TP101.1, TP102.1, TP103.1, TP104.1, TP105.1, TP106.1, TP107.1, TP108.1, TP109.1, TP110.1, TP111.1, TP112.1; also elsewhere on the board
unnamed: C101.2, J101.5 (Ext)
unnamed: C102.1, J102.5 (Ext)
